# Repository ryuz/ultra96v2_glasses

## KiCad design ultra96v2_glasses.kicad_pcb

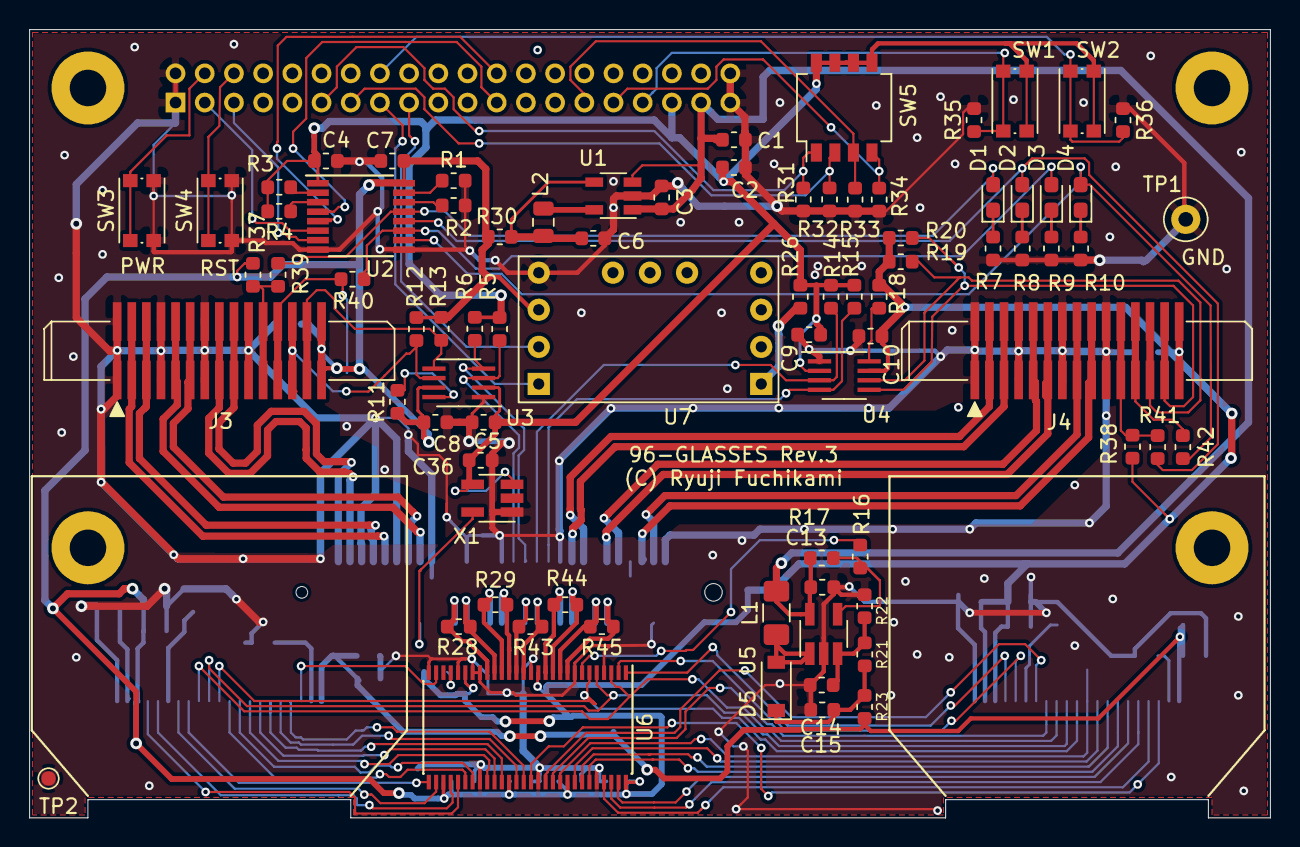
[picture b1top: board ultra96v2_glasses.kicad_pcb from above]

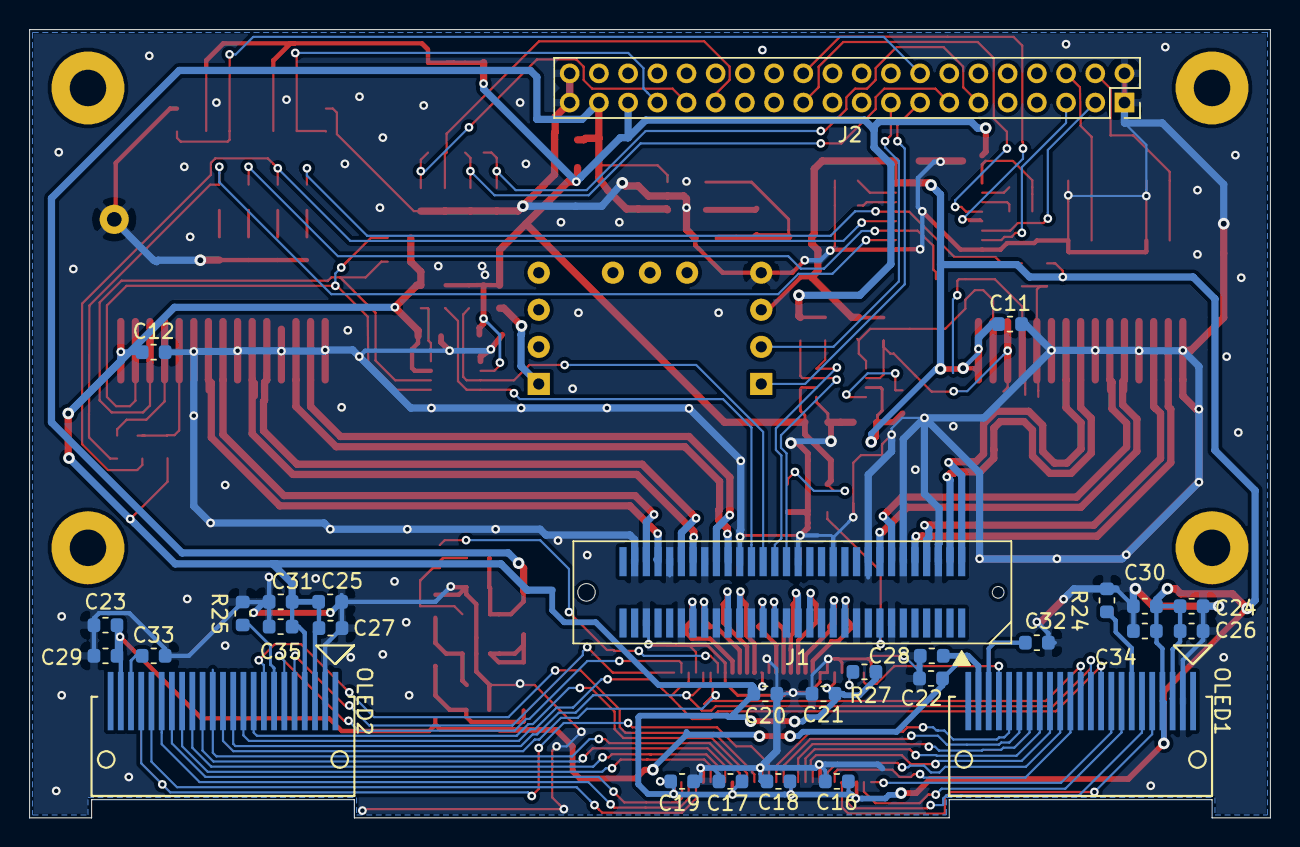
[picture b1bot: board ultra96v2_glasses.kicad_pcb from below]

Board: 2 copper layers, 85.0 x 54.0 mm, 109 parts (29 on the bottom side), 108 nets.

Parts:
C1, C2, C3, C6: 10uF; C_0603_1608Metric
C4, C5, C7, C8, C9, C10, C11, C12, C16, C17, C18, C19, C20, C21, C26, C27, C34, C35, C36: 0.1uF; C_0603_1608Metric
C13: 2.2uF; C_0603_1608Metric
C14: 220pF/25V; C_0603_1608Metric
C15, C32, C33: 4.7uF 25V; C_0603_1608Metric
C22, C23: 10uF 25V; C_0603_1608Metric
C24, C25, C30, C31: 4.7uF; C_0603_1608Metric
C28, C29: 0.1uF 25V; C_0603_1608Metric
D1, D2, D3, D4: SML-512MWT86; LED_0603_1608Metric_Pad1.05x0.95mm_HandSolder
D5: MBR0520LT1G; D_SOD-123
J1: 61083-064402LF; 61083-063402LF
J2: 10075024-G01-20ULF; PinSocket_2x20_P2.00mm_Vertical
J3, J4: 1-1734248-5; 55510-140LF_handsolder
L1: 10uH CBC2518T100M; L_1206_3216Metric_Pad1.42x1.75mm_HandSolder
L2: 2.2uH_2012; L_0805_2012Metric
OLED1, OLED2: UG-9664HDDAG01
R1, R2, R3, R4, R11, R16, R18, R23, R26, R27, R30, R37, R38: 0; R_0603_1608Metric
R5, R6, R12, R13, R14, R15, R19, R20, R31, R32, R33, R34, R35, R36: 4.7k; R_0603_1608Metric
R7, R8, R9, R10, R28, R29, R43, R44, R45: 100; R_0603_1608Metric
R17: 51k; R_0603_1608Metric
R21: 140k; R_0603_1608Metric
R22: 13.3k; R_0603_1608Metric
R24, R25: 1.1M; R_0603_1608Metric
R39, R40, R41, R42: <0>; R_0603_1608Metric
SW1, SW2, SW3, SW4: KMR213G LFG; SW_Push_1P1T_NO_CK_KMR2
SW5: GDH04S04; SW_DIP_SPSTx04_Slide_Omron_A6H-4101_W6.15mm_P1.27mm
TP1: TP_GND; TestPoint_Loop_D1.80mm_Drill1.0mm_Beaded
TP2: TP_GND; TestPoint_Pad_D1.0mm
U1: LM3671MF-3.3; TSOT-23-5
U2: SN74AVC4T245PW; TSSOP-16_4.4x5mm_P0.65mm
U3, U4: PCA9306DCTR
U5: LM2733XMF; SOT-23-5_HandSoldering
U6: THC63LVDR84C; TSSOP-56_6.1x14mm_P0.5mm
U7: SS-MPU-9250
X1: SIT2024BA-S3-18E-25.000000G; SOT-23-5_HandSoldering

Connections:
+1V8: C2.1, C4.1, C5.1, C9.1, C36.1, J2.35, R3.2, R4.2, R5.2, R6.2, R14.2, R15.2, R26.2, SW1.2, SW2.2, SW5.5, SW5.6, SW5.7, SW5.8, U2.1, U3.2, U4.2, X1.3, X1.4
+3V3: C7.1, C8.1, C10.1, C11.1, C12.1, C16.1, C17.1, C18.1, C19.1, C20.1, C21.1, C24.1, C25.1, C26.1, C27.1, C30.1, C31.1, C34.1, C35.1, J3.15, J4.15, OLED1.3, OLED1.4, OLED2.3, OLED2.4, R11.1, R12.1, R13.1, R18.1, R19.1, R20.1, R27.2, R30.1, R37.2, R38.2, U2.16, U3.7, U4.7, U6.13, U6.23, U6.31, U6.40, U6.48, U6.56, U7.J1-3
+5V: C1.1, C3.1, C13.1, J2.37, L1.2, R17.1, U1.1, U1.3, U5.5
/CAM0_CLK: J3.12, R40.1
/CAM0_GPIO: J3.11, R37.1, R39.1
/CAM0_SCL: J3.13, R12.2, U3.6
/CAM0_SDA: J3.14, R13.2, U3.5
/CAM1_CLK: J4.12, R42.1
/CAM1_GPIO: J4.11, R38.1, R41.1
/CAM1_SCL: J4.13, R19.2, U4.6
/CAM1_SDA: J4.14, R20.2, U4.5
/HS_CSI0_CLK_N: J1.4, J3.8
/HS_CSI0_CLK_P: J1.2, J3.9
/HS_CSI0_D0_N: J1.10, J3.2
/HS_CSI0_D0_P: J1.8, J3.3
/HS_CSI0_D1_N: J1.16, J3.5
/HS_CSI0_D1_P: J1.14, J3.6
/HS_CSI0_MCLK: J1.15, X1.5
/HS_CSI1_CLK_N: J1.56, J4.8
/HS_CSI1_CLK_P: J1.54, J4.9
/HS_CSI1_D0_N: J1.44, J4.2
/HS_CSI1_D0_P: J1.42, J4.3
/HS_CSI1_D1_N: J1.50, J4.5
/HS_CSI1_D1_P: J1.48, J4.6
/HS_DSI_CLK_N: J1.23, R28.1, U6.19
/HS_DSI_CLK_P: J1.21, R28.2, U6.20
/HS_DSI_D0_N: J1.29, R29.1, U6.17
/HS_DSI_D0_P: J1.27, R29.2, U6.18
/HS_DSI_D1_N: J1.35, R43.1, U6.15
/HS_DSI_D1_P: J1.33, R43.2, U6.16
/HS_DSI_D2_N: J1.41, R44.1, U6.11
/HS_DSI_D2_P: J1.39, R44.2, U6.12
/HS_DSI_D3_N: J1.47, R45.1, U6.9
/HS_DSI_D3_P: J1.45, R45.2, U6.10
/HS_I2C2_SCL: J1.32, R5.1, U3.3
/HS_I2C2_SDA: J1.34, R6.1, U3.4
/HS_I2C3_SCL: J1.36, R14.1, U4.3
/HS_I2C3_SDA: J1.38, R15.1, U4.4
/LS_3V3_GPIO_0: D3.2, R40.2, U2.11
/LS_3V3_GPIO_1: D4.2, R42.2, U2.10
/LS_3V3_PS_GPIO_0: D1.2, R39.2, U2.13
/LS_3V3_PS_GPIO_1: D2.2, R41.2, U2.12
/LS_GPIO_0: J2.3, U2.6
/LS_GPIO_1: J2.5, U2.7
/LS_GPIO_4: J2.11, R31.1, SW5.1
/LS_GPIO_5: J2.13, R32.1, SW5.2
/LS_GPIO_6: J2.29, R33.1, SW5.3
/LS_GPIO_7: J2.31, R34.1, SW5.4
/LS_GPIO_8: J2.33, R35.1, SW1.1
/LS_GPIO_9: J2.16, R36.1, SW2.1
/LS_I2C0_SCL: J2.15, U7.J1-1
/LS_I2C0_SDA: J2.17, U7.J1-2
/LS_PS_GPIO_0: J2.23, U2.4
/LS_PS_GPIO_1: J2.24, U2.5
/OLED0_BS1: OLED1.5, U6.33
/OLED0_BS2: OLED1.6, U6.32
/OLED0_CS: OLED1.8, U6.30
/OLED0_D0: OLED1.13, U6.34
/OLED0_D1: OLED1.14, U6.35
/OLED0_D2: OLED1.15, U6.37
/OLED0_D3: OLED1.16, U6.38
/OLED0_D4: OLED1.17, U6.39
/OLED0_D5: OLED1.18, U6.41
/OLED0_D6: OLED1.19, U6.42
/OLED0_D7: OLED1.20, U6.27
/OLED0_IREF: OLED1.7, R24.2
/OLED0_RES: OLED1.9, U6.29
/OLED0_VCOMH: C32.1, OLED1.21
/OLED1_BS1: OLED2.5, U6.1
/OLED1_BS2: OLED2.6, U6.2
/OLED1_CS: OLED2.8, U6.45
/OLED1_D0: OLED2.13, U6.47
/OLED1_D1: OLED2.14, U6.49
/OLED1_D2: OLED2.15, U6.50
/OLED1_D3: OLED2.16, U6.51
/OLED1_D4: OLED2.17, U6.55
/OLED1_D5: OLED2.18, U6.54
/OLED1_D6: OLED2.19, U6.53
/OLED1_D7: OLED2.20, U6.43
/OLED1_IREF: OLED2.7, R25.2
/OLED1_RES: OLED2.9, U6.46
/OLED1_VCOMH: C33.1, OLED2.21
/OLED_DC: OLED1.10, OLED2.10, U6.3
/OLED_E: OLED1.12, OLED2.12, U6.6
/OLED_RW: OLED1.11, OLED2.11, U6.5
/PWR_EN: R16.1, U6.7
/PWR_PB_N: J2.4, SW3.1
/RST_PB_N: J2.6, SW4.1
/VCC_FB: C14.1, R21.2, R22.1, U5.3
/VCC_OUT: C15.1, D5.1, R21.1, R23.1
/VCC_SHDN: R16.2, R17.2, U5.4
/VCC_SW: D5.2, L1.1, U5.1
GND: C1.2, C2.2, C3.2, C4.2, C5.2, C6.2, C7.2, C8.2, C9.2, C10.2, C11.2, C12.2, C13.2, C14.2, C15.2, C16.2, C17.2, C18.2, C19.2, C20.2, C21.2, C22.2, C23.2, C24.2, C25.2, C26.2, C27.2, C28.2, C29.2, C30.2, C31.2, C32.2, C33.2, C34.2, C35.2, C36.2, J1.6, J1.12, J1.13, J1.18, J1.19, J1.24, J1.25, J1.30, J1.31, J1.37, J1.40, J1.43, J1.46, J1.49, J1.52, J1.55, J1.58, J2.1, J2.2, J2.39, J2.40, J3.1, J3.4, J3.7, J3.10, J4.1, J4.4, J4.7, J4.10, OLED1.2, OLED2.2, R1.2, R2.2, R7.1, R8.1, R9.1, R10.1, R22.2, R24.1, R25.1, R31.2, R32.2, R33.2, R34.2, R35.2, R36.2, SW3.2, SW4.2, TP1.1, TP2.1, U1.2, U2.8, U2.9, U3.1, U4.1, U5.2, U6.4, U6.8, U6.14, U6.21, U6.22, U6.24, U6.28, U6.36, U6.44, U6.52, U7.J1-4, X1.1
unnamed: C6.1, L2.1, R30.2, U1.4
unnamed: D1.1, R7.2
unnamed: D2.1, R8.2
unnamed: D3.1, R9.2
unnamed: D4.1, R10.2
unnamed: L2.2, U1.5
unnamed: R1.1, U2.15
unnamed: R2.1, U2.14
unnamed: R3.1, U2.2
unnamed: R4.1, U2.3
unnamed: R11.2, U3.8
unnamed: R18.2, U4.8
unnamed: R26.1, U7.J3-1
unnamed: R27.1, U6.25
VCC: C22.1, C23.1, C28.1, C29.1, OLED1.22, OLED2.22, R23.2

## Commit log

2020-03-08 rev2
2020-08-08 update rev3
